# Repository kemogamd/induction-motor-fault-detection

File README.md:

# Induction Motor Fault Detection Using Machine Learning

This repository contains the full implementation of my BSc Thesis project, which develops a complete predictive maintenance system for induction motors. The system integrates a Simulink digital twin, synthetic time-series generation, a custom analog vibration signal-conditioning PCB, and a Python machine learning pipeline.  
Seven ML models were benchmarked for early-stage fault identification, achieving 92–100% classification accuracy across electrical and mechanical motor faults.

---

## Key Features

- **Digital Twin Model (Simulink):**  
  Full 4 kW induction motor model generating over **250,000 labeled samples** for multiple fault conditions.

- **Machine Learning Pipeline:**  
  Implemented and benchmarked 7 models:  
  - XGBoost  
  - MLP  
  - SVM  
  - Random Forest  
  - 1D CNN  
  - ResNet1D  
  - CNN–LSTM hybrid model  

- **Real Sensor Integration (ESP32):**  
  Real-time vibration acquisition using an ADXL335 analog accelerometer.  
  Data streamed over serial → Python preprocessing → ML inference.

- **Custom Hardware (KiCad):**  
  Designed a Vibration Signal Conditioning Board featuring:  
  - ADXL335 accelerometer  
  - AC-coupling and bias reference  
  - MCP6002 op-amp buffer  
  - Output stage optimized for ESP32 ADC input  

- **Real-Time Fault Classification:**  
  Edge-deployable fault detection with sub-second inference time.

---

## Project Structure

induction-motor-fault-detection/  
├── ml_pipeline/  
│   ├── general.py  
│   ├── PreprocessDataset.py  
│   ├── Train_CNN.py  
│   ├── Train_CNN_LSTM.py  
│   ├── Train_MLP.py  
│   ├── Train_ResNet1D.py  
│   ├── Train_Rf.py  
│   ├── Train_SVM.py  
│   └── Train_XGBoost.py  
│  
├── simulink_model/  
│   └── induction_motor_digital_twin.slx  
│   └── extdata.m  
│   └── induction_motor_digital_twin.slx.r2018a
│   └── sim_data_healthy.csv
│  
├── hardware/  
│   └── Vibration Signal Conditioning Board KICAD/  
│       ├── Vibration Signal Conditioning Board.kicad_pro  
│       ├── Vibration Signal Conditioning Board.kicad_sch  
│       ├── Vibration Signal Conditioning Board.kicad_pcb  
│       ├── Vibration Signal Conditioning Board.kicad_prl  
│       ├── New_Library.kicad_sym  
│       └── backups/  
│  
├── requirements.txt  
└── README.md  

---

## Machine Learning Workflow

1. **Signal generation** using Simulink digital twin.  
2. **Data preprocessing:**  
   - filtering  
   - segmentation  
   - statistical and frequency-domain feature extraction  
3. **Model training** using Scikit-Learn / PyTorch / TensorFlow.  
4. **Model evaluation** using accuracy, F1-score, and confusion matrices.  
5. **Real-time inference** using ESP32 vibration data → Python pipeline.

---

## Results

- Achieved **92–100% classification accuracy** across all fault categories.  
- ResNet1D and CNN–LSTM provided the best overall performance.  
- System validated using both synthetic and real ESP32 vibration data.

---

## Tech Stack

- **Python**, **NumPy**, **Pandas**, **Scikit-Learn**, **PyTorch/TensorFlow**  
- **MATLAB Simulink**  
- **ESP32**, **ADXL335 accelerometer**  
- **Serial Communication**  
- **Git/GitHub**

---

## How to Run

### 1. Install dependencies
pip install -r requirements.txt

### 2. Run preprocessing
python ml_pipeline/PreprocessDataset.py

### 3. Train models
python ml_pipeline/Train_ResNet1D.py  
(or any other model script)

### 4. Evaluate models
Each training script outputs metrics and logs.

### 5. Real-time inference with ESP32
1. Upload the code under `esp32/` to your ESP32.  
2. Connect via serial and run the inference script (if used).

---

## Future Work

- Deploy models on microcontrollers (TinyML).  
- Improve synthetic-to-real domain adaptation.  
- Add a GUI-based real-time monitoring dashboard.

---

## Author

**Kareem Hussein**  
Electrical Engineering | University of Debrecen  
GitHub: https://github.com/kemogamd  
Email: khaledokareem@gmail.com

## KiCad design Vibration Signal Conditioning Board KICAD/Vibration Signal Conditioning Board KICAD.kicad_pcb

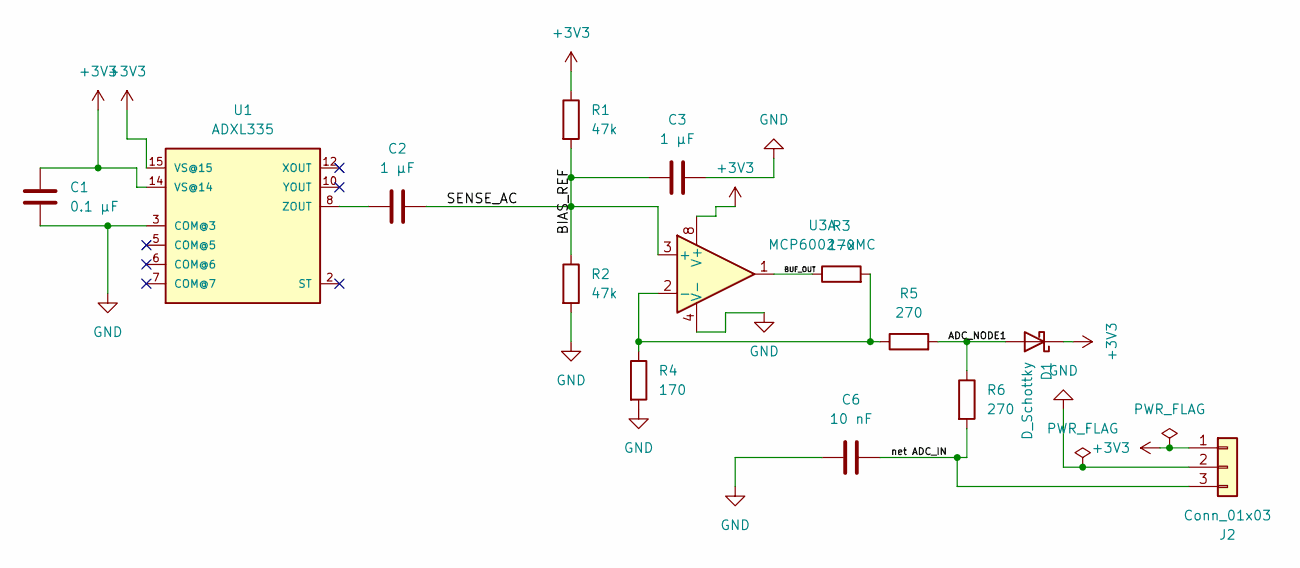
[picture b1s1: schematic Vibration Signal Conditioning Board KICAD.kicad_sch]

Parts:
C1: 0.1 µF; R_0603_1608Metric
C2, C3: 1 µF; C_0603_1608Metric
C6: 10 nF; C_0603_1608Metric
D1: D_Schottky; D_0603_1608Metric
J2: Conn_01x03; PinHeader_1x03_P1.00mm_Vertical_SMD_Pin1Left
R1, R2: 47k; R_0603_1608Metric
R3, R4: 170; R_0603_1608Metric
R5, R6: 270; R_0603_1608Metric
U1: ADXL335; QFN-16-1EP_4x4mm_P0.65mm_EP2.5x2.5mm
U3: MCP6002-xMC; DFN-8-1EP_3x2mm_P0.5mm_EP1.75x1.45mm

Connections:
+3V3: C1.2, D1.1 (K), J2.1, R1.1, U1.14 (VS@14), U1.15 (VS@15), U3.8 (V+)
/ADC_NODE1: D1.2 (A), R5.2, R6.1
/BIAS_REF: C2.2, C3.1, R1.2, R2.1, U3.3 (+)
/BUF_OUT: R3.1, U3.1
/net ADC_IN: C6.2, J2.3, R6.2
GND: C1.1, C3.2, C6.1, J2.2, R2.2, R4.2, U1.3 (COM@3), U3.4 (V-), U3.9 (V-)
unnamed: C2.1, U1.8 (ZOUT)
unnamed: R3.2, R4.1, R5.1, U3.2 (-)

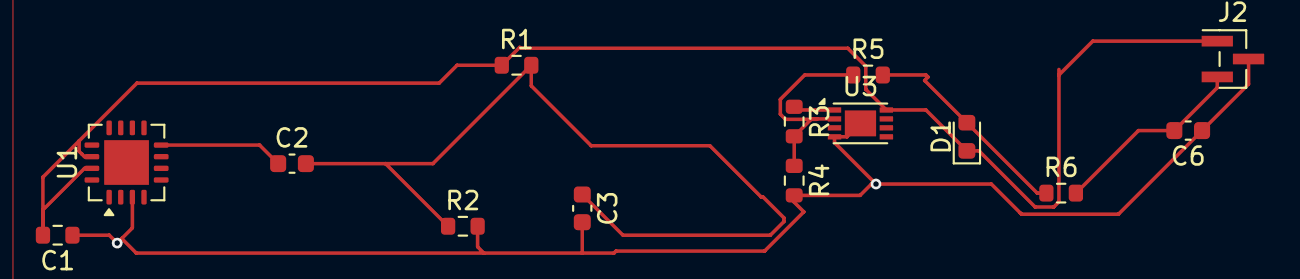
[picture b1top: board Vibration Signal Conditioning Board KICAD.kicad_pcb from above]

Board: 2 copper layers, 14 parts (0 on the bottom side), 8 nets.

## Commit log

2025-11-29 Revise README for clarity and completeness
    Updated README to enhance project description and structure, added key features, machine learning workflow, results, tech stack, instructions on running the project, future work, license, and author 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
2025-11-29 Delete License section from README
    Removed License section from README.
2025-11-29 Revise README for clarity and project overview
    Updated README to reflect project details and structure.
2025-11-29 Update README with new files in simulink_model
    Added new files to the simulink_model directory.
2025-11-29 Add Simulink model and related data files
